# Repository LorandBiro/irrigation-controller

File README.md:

# Irrigation Controller

This repository contains the software, hardware design, and documentation of a smart irrigation controller. The system is designed and created for personal use.

## Features
- Automated irrigation using 4 solenoid valves.
- Configuration and control through web interface.
- Suspension of irrigation when it's raining.
- Short-circuit detection.
- DIN rail mounting.

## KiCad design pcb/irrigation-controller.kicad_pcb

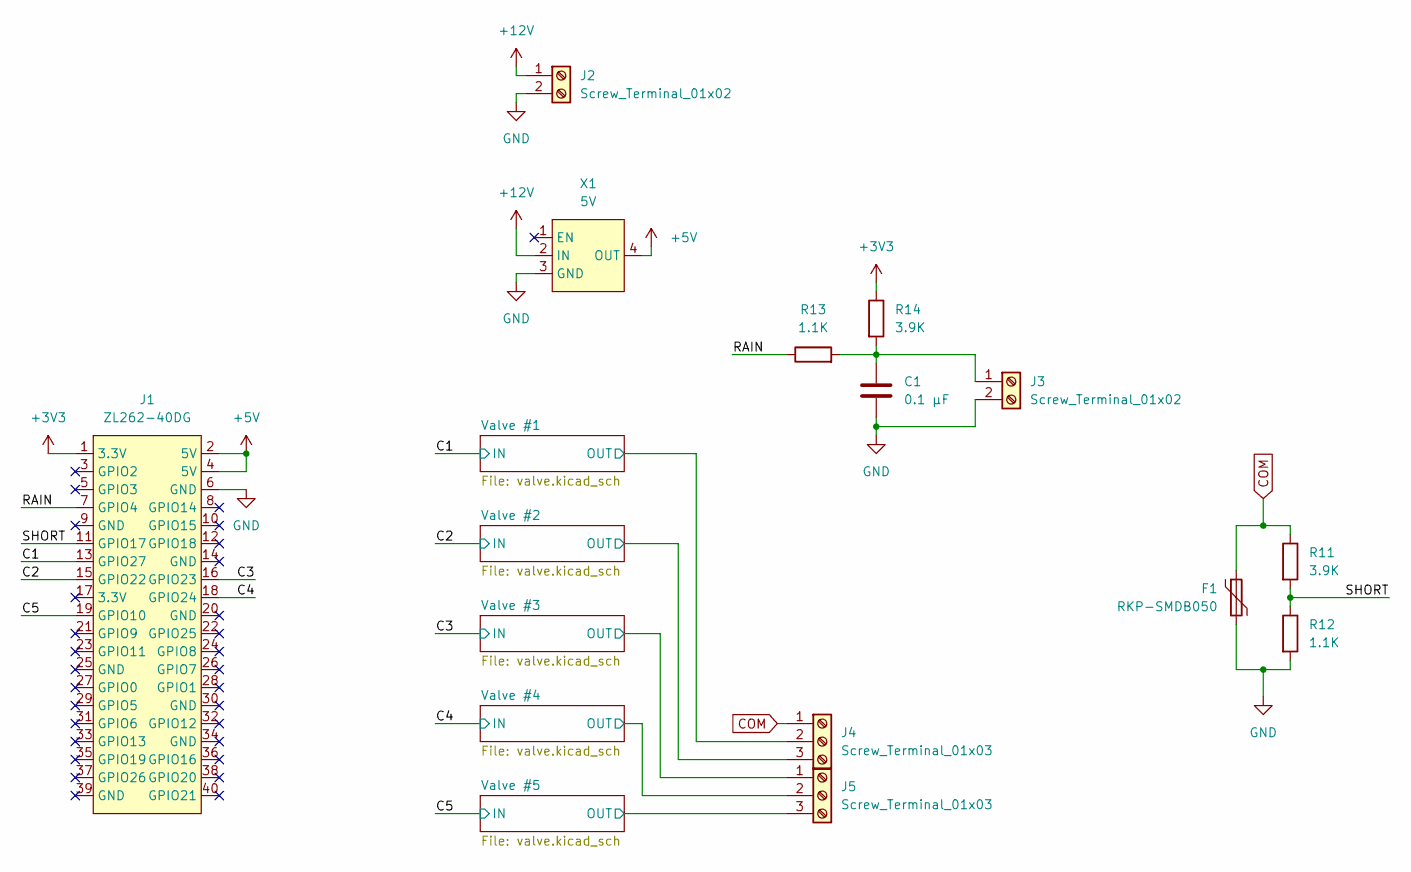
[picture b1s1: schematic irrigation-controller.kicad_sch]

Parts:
C1: 0.1 µF; C_0805_2012Metric
F1: RKP-SMDB050; Fuse_1206_3216Metric
J1: ZL262-40DG; PinSocket_2x20_P2.54mm_Vertical
J2, J3: Screw_Terminal_01x02; MX5-2P-BK
J4, J5: Screw_Terminal_01x03; MX5-3P-BK
R11, R14: 3.9K; R_0805_2012Metric
R12, R13: 1.1K; R_0805_2012Metric
X1: 5V; STDN-3A24-ADJ

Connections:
+3V3: J1.1 (3.3V), R14.1
+5V: J1.2 (5V), J1.4 (5V), X1.4 (OUT)
+12V: J2.1, X1.2 (IN); also elsewhere on the board
/C1: J1.13 (GPIO27); also elsewhere on the board
/C2: J1.15 (GPIO22); also elsewhere on the board
/C3: J1.16 (GPIO23); also elsewhere on the board
/C4: J1.18 (GPIO24); also elsewhere on the board
/C5: J1.19 (GPIO10); also elsewhere on the board
/RAIN: J1.7 (GPIO4), R13.1
/SHORT: J1.11 (GPIO17), R11.2, R12.1
/Valve #1/OUT: J4.2; also elsewhere on the board
/Valve #2/OUT: J4.3; also elsewhere on the board
/Valve #3/OUT: J5.1; also elsewhere on the board
/Valve #4/OUT: J5.2; also elsewhere on the board
/Valve #5/OUT: J5.3; also elsewhere on the board
COM: F1.1, J4.1, R11.1; also elsewhere on the board
GND: C1.2, F1.2, J1.6 (GND), J2.2, J3.2, R12.2, X1.3 (GND); also elsewhere on the board
unnamed: C1.1, J3.1, R13.2, R14.2

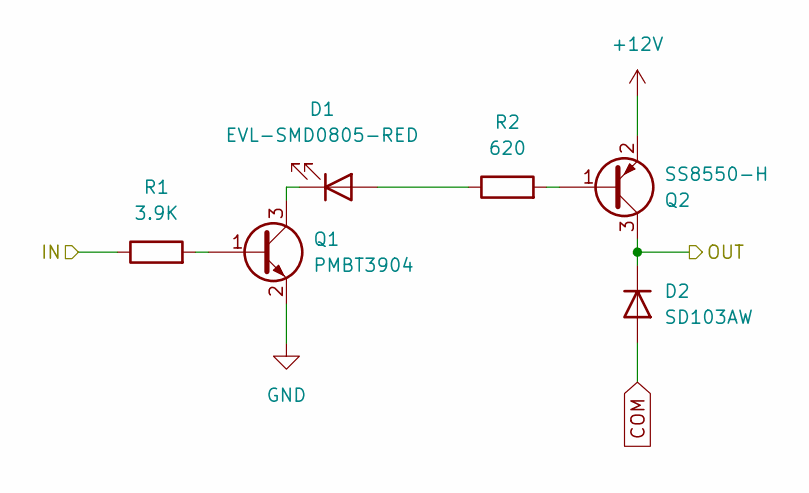
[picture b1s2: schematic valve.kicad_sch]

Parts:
D1: EVL-SMD0805-RED; LED_0805_2012Metric_Pad1.15x1.40mm_HandSolder
D2: SD103AW; D_SOD-123
Q1: PMBT3904; TSOT-23
Q2: SS8550-H; TSOT-23
R1: 3.9K; R_0805_2012Metric_Pad1.20x1.40mm_HandSolder
R2: 620; R_0805_2012Metric

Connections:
+12V: Q2.2 (E); also elsewhere on the board
/C1: R1.1; also elsewhere on the board
/Valve #1/OUT: D2.1 (K), Q2.3 (C); also elsewhere on the board
COM: D2.2 (A); also elsewhere on the board
GND: Q1.2 (E); also elsewhere on the board
unnamed: D1.2 (A), R2.1
unnamed: D1.1 (K), Q1.3 (C)
unnamed: Q1.1 (B), R1.2
unnamed: Q2.1 (B), R2.2

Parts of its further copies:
D3, D5, D7, D9: EVL-SMD0805-RED; LED_0805_2012Metric_Pad1.15x1.40mm_HandSolder
D4, D6, D8, D10: SD103AW; D_SOD-123
Q3, Q5, Q7, Q9: PMBT3904; TSOT-23
Q4, Q6, Q8, Q10: SS8550-H; TSOT-23
R3, R5, R7, R9: 3.9K; R_0805_2012Metric_Pad1.20x1.40mm_HandSolder
R4, R6, R8, R10: 620; R_0805_2012Metric

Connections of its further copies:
+12V: Q4.2 (E), Q6.2 (E), Q8.2 (E), Q10.2 (E); also elsewhere on the board
/C2: R3.1; also elsewhere on the board
/C3: R5.1; also elsewhere on the board
/C4: R7.1; also elsewhere on the board
/C5: R9.1; also elsewhere on the board
/Valve #2/OUT: D4.1 (K), Q4.3 (C); also elsewhere on the board
/Valve #3/OUT: D6.1 (K), Q6.3 (C); also elsewhere on the board
/Valve #4/OUT: D8.1 (K), Q8.3 (C); also elsewhere on the board
/Valve #5/OUT: D10.1 (K), Q10.3 (C); also elsewhere on the board
COM: D4.2 (A), D6.2 (A), D8.2 (A), D10.2 (A); also elsewhere on the board
GND: Q3.2 (E), Q5.2 (E), Q7.2 (E), Q9.2 (E); also elsewhere on the board
unnamed: D3.2 (A), R4.1
unnamed: D3.1 (K), Q3.3 (C)
unnamed: D5.2 (A), R6.1
unnamed: D5.1 (K), Q5.3 (C)
unnamed: D7.2 (A), R8.1
unnamed: D7.1 (K), Q7.3 (C)
unnamed: D9.2 (A), R10.1
unnamed: D9.1 (K), Q9.3 (C)
unnamed: Q3.1 (B), R3.2
unnamed: Q4.1 (B), R4.2
unnamed: Q5.1 (B), R5.2
unnamed: Q6.1 (B), R6.2
unnamed: Q7.1 (B), R7.2
unnamed: Q8.1 (B), R8.2
unnamed: Q9.1 (B), R9.2
unnamed: Q10.1 (B), R10.2

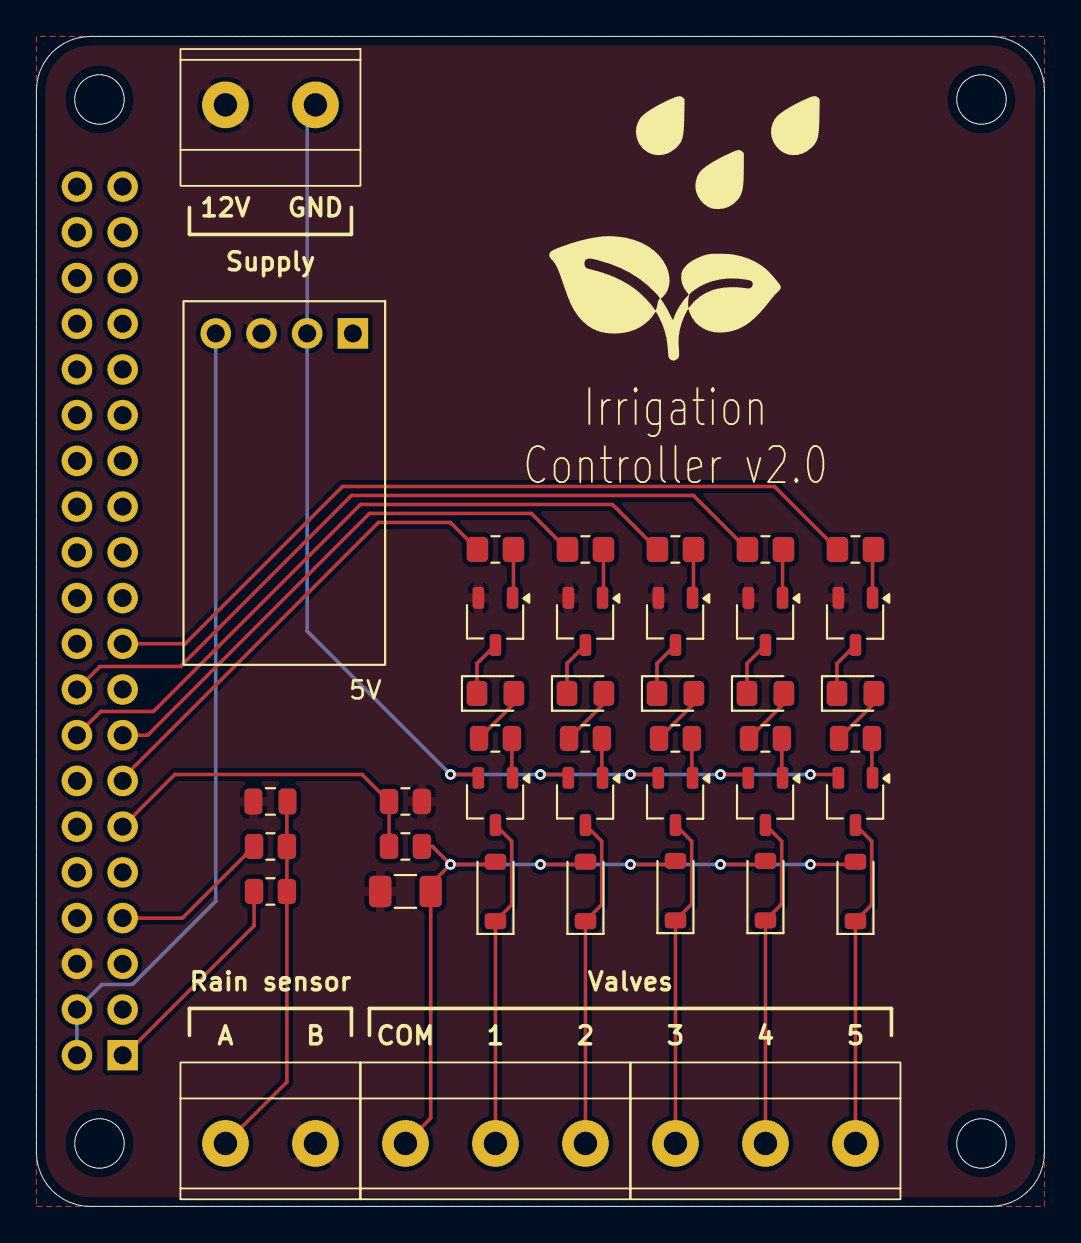
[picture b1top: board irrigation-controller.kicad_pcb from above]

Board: 2 copper layers, 56.0 x 65.0 mm, 42 parts (1 on the bottom side), 38 nets.

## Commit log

2024-03-22 Add basic README
2024-03-22 Add PCB design
2024-04-03 Update resistor values based on availability
2024-04-26 Add DIN rail mounting clip
2024-05-28 Update mount design
    The first version's spring is too weak and the device is very loose on
    the DIN rail. The spring thickness was increased and the slider position
    is modified so the spring will be under tension when it's on the DIN
    rail. Hopefully this tension will make the device more stable.
2024-05-28 Rename case to mount
2024-06-08 docs and src
2024-06-12 Add basic web app: valves can be opened and closed manually
2024-06-13 Add valve names
2024-06-13 Add valve delay
2024-06-13 Add live status update
2024-06-13 Add deploy script
2024-06-13 Add documentation
2024-06-13 Guard against race-conditions
2024-06-13 Reorganize Core
2024-06-13 Add ProgramController
2024-06-13 Small improvements around the manual control page
2024-06-13 Add run program page
2024-06-13 Make log messages fit in one line
2024-06-13 Close valves on startup
2024-06-13 Configure debug logging only for the application
2024-06-15 Open/close valves with the same button
2024-06-15 Remove redundant GPIO calls
2024-06-15 Move ValveConfig to Domain
2024-06-15 Add status display
2024-06-15 Add Step and Stop buttons
2024-06-15 Fix missing Dispose method from Home page
2024-06-15 Move valve control to a component
2024-06-15 Move manual program to a component
2024-06-15 Move status to a component
2024-06-15 Minor UI improvement
2024-06-15 Rename step to skip
2024-06-15 Add rain sensor
2024-06-15 Add short circuit sensor
2024-06-15 Change abstraction from IGpio to IValves
2024-06-16 Log short circuit clear
2024-06-16 Add ValveRepository, store IsDefective, guard against opening defective valves
2024-06-16 Reorganize Program.cs
2024-06-16 Disable defective valve buttons
2024-06-16 Add fix valve button
2024-06-16 Simplify manual program and disable defective valves
2024-06-16 Move use-cases to root directory
2024-06-16 Add basic irrigation log
2024-06-16 Add log viewer
2024-06-16 Restore create directory call for AppDataPath
2024-06-16 Add creating AppDataPath to setup.md
2024-06-16 Rename GpioSimulator to DevTools
2024-06-17 Reorder Home page again
2024-06-17 Add sunrise scheduler
2024-06-18 Change irrigation log to typed event stream
2024-06-18 Rename valve to zone
2024-06-18 Add zone enabled configuration
2024-06-18 Improve irrigation stop reasons
2024-06-18 Move IIrrigationLog and IZoneRepository to Domain
2024-06-18 Add editorconfig and change to file-scoped namespace
2024-06-18 Add KillSignal to service for graceful shutdown
2024-06-19 Rename ProgramStep to ZoneDuration
2024-06-19 Rename irrigation-events.json to irrigation-log.json
2024-06-19 Consolidate zone numbering
2024-06-19 Tweak IrrigationLog logging
2024-06-20 Implement fallback algorithm
2024-06-20 Add scripts for raspberry pi
2024-06-21 Simplify logging
2024-06-21 Disable ZoneControl if a program is running
2024-06-21 Create soil moisture estimator
2024-06-21 Rename Controllers to Services
2024-06-21 Rename irrigation start and stop reasons
2024-06-21 Rename PrecipitationPerRun to MaxPrecipitation
2024-06-21 Rename Algorithm to Schedule
2024-06-21 Add basic Prometheus metrics endpoint
2024-06-21 Add open zone and short circuit to Prometheus
2024-06-22 Rewrite SoilMoistureEstimator
2024-06-22 Rename precipitation rate to irrigation rate
2024-06-22 Publish csproj instead of sln
2024-06-22 Show logs at the end of publish
2024-06-22 Consolidate prometeus metrics name
2024-06-22 Simplify soil moisture estimator
2024-06-22 Integrate with OpenMeteo API
2024-06-22 Add temperature data
2024-06-22 Add proper metric name prefix
2024-06-22 Add logging to OpenMeteoApi
2024-06-22 Adjust crop coefficients
2024-06-25 Change SoilMoistureEstimator from % to mm
2024-07-08 Use weather forecast for irrigation decision making
2024-07-12 Change the irrigation algorithm to avoid drying out
2024-07-12 Reset zone parameters to a meaningful default
2024-07-12 Add zone splitting
2024-07-12 Remove fallback schedule as open reason
    It no longer makes sense, there's no separate algorithm if there's no internet.
2024-08-22 Start the soil moisture estimator from max
2024-08-22 Adjust irrigation configuration
2024-08-30 Add logging to SunriseEventHandler
2024-08-31 Change to systemd logging format
2024-08-31 Change OpenMeteoApi logging to trace
2024-08-31 Start the process only after successful time sync
2024-09-07 Fix double/triple sunrise triggering and add logging
2024-10-24 Change terminal, add another output, add hardware debouncing
2024-10-24 Adjust components based on availability
2024-11-02 Skip irrigation if temperature is too low
